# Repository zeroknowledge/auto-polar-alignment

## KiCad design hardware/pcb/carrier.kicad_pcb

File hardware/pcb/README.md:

# APA-CARRIER rev A -- carrier PCB for the Auto Polar Alignment base

Generated by `generate.py` (single reproducible script, see the end of this file). Authoritative design: `SPEC.md`.
**KiCad itself was NOT available: the `.kicad_pcb` / `.kicad_sch` were written by this script and parsed back with kiutils only.
KiCad ERC and DRC have NOT been run and are still outstanding.** Pours are stored as zone outlines; press B (fill all zones) in KiCad.

Board: 85 x 60 mm, 1.6 mm FR4, 2 layers, 2 mm corner radius, four M3 NPTH holes (3.2 mm).
Tallest component: 17.1 mm above the top face (18.7 mm above the bottom face): the plugged-in TMC2209 module with heatsink (assumed envelope). Next tallest: PTC 14 mm, C1 12 mm, C2/C3 11 mm, screw terminals 10 mm (all assumed typical). The J1 socket protrudes 8.5 mm below the board.

## Spec problems found (SPEC.md was not silently changed)

1. **TMC2209 socket row spacing (mechanical, was a real error)**: SPEC.md said 15.24 mm, so a real module would not plug in; the real Pololu/SilentStepStick pin rows are 12.70 mm apart (15.24 x 20.32 mm is the module *size*). The lead has since corrected SPEC.md; the generator default is now 12.70 mm (`--driver-row-spacing`).
2. **Via vs. annular-ring rule**: vias 0.6/0.3 mm have a 0.15 mm ring while "plated through-hole annular ring >= 0.3 mm" is also stated. I applied 0.3 mm to component holes and 0.15 mm to vias (fab capability not checked).
3. **PTC voltage rating**: the TVS (1.5KE18A) clamps near 25 V, so choose PTCs rated for at least 24-30 V; many 16 V radial PTCs do not have a 5.08 mm lead pitch (not verified against a specific part).
4. 3V3 track width not specified (0.5 mm used). With D1 in series the motor rail is about 0.4-0.5 V below the PD voltage (not an error).

## Files

| File | What |
|---|---|
| `netlist.json` | single source of truth (parts, pins, nets, NC pins); `carrier.net` is the same netlist in KiCad format |
| `diagrams/` | schematic sheets and system wiring diagram (SVG/PDF/PNG), drawn from `netlist.json` by `make_diagrams.py` (not part of this script) |
| `carrier.kicad_pro`, `carrier.kicad_pcb`, `carrier.kicad_sch` | KiCad 8 project (written, not opened in KiCad) |
| `fab/carrier-*.gtl/.gbl/.gts/.gbs/.gtp/.gto/.gbo/.gm1`, `fab/carrier-PTH.drl`, `fab/carrier-NPTH.drl`, `fab/carrier_gerbers.zip` | Gerber RS-274X (F.Cu, B.Cu, F/B mask, F paste, F/B silkscreen, Edge.Cuts) and Excellon drills |
| `fab/gerber_reparse_preview.png` | the Gerbers re-read with gerbonara and re-drawn (proof they parse) |
| `carrier_bom.csv`, `carrier_cpl.csv` | BOM (grouped, plug-in items listed but marked not soldered) and SMD pick-and-place |
| `carrier_outline.dxf`, `carrier_board.stl` | outline/holes/component keep-outs/Pi outline; extruded board + component envelopes |
| `carrier_top.png`, `carrier_bottom.png` | renders |
| `verification_report.json` | every number quoted below |

## Pin map

### Pi header J1 (female socket on the BOTTOM side; pin 1 = square pad, lower-left row when viewed from the top)

| Pi pin | GPIO | Net |
|---|---|---|
| 1 |  | 3V3 |
| 2 |  | 5V_PI |
| 3 | GPIO2 SDA1 | SDA |
| 4 |  | 5V_PI |
| 5 | GPIO3 SCL1 | SCL |
| 6 |  | GND |
| 7 |  | NC |
| 8 | GPIO14 TXD | UART_TX_RAW |
| 9 |  | GND |
| 10 | GPIO15 RXD | UART_BUS |
| 11 | GPIO17 | STEP_AZ |
| 12 |  | NC |
| 13 | GPIO27 | DIR_AZ |
| 14 |  | GND |
| 15 | GPIO22 | EN_AZ |
| 16 | GPIO23 | STEP_ALT |
| 17 |  | 3V3 |
| 18 | GPIO24 | DIR_ALT |
| 19 |  | NC |
| 20 |  | GND |
| 21 |  | NC |
| 22 | GPIO25 | EN_ALT |
| 23 |  | NC |
| 24 |  | NC |
| 25 |  | GND |
| 26 |  | NC |
| 27 |  | NC |
| 28 |  | NC |
| 29 | GPIO5 | ES_AZ_MIN |
| 30 |  | GND |
| 31 | GPIO6 | ES_AZ_MAX |
| 32 |  | NC |
| 33 | GPIO13 | ES_ALT_MIN |
| 34 |  | GND |
| 35 | GPIO19 | ES_ALT_MAX |
| 36 |  | NC |
| 37 | GPIO26 | SPARE |
| 38 |  | NC |
| 39 |  | GND |
| 40 |  | NC |

27 pins used, 13 NC (pins 7, 12, 19, 21, 23, 24, 26, 27, 28, 32, 36, 38, 40 carry no copper connection).

### TMC2209 sockets (rows 12.7 mm apart; U1 = azimuth, U2 = altitude)

| U1/U2 row A pin | U1 net | U2 net | row B pin | U1 net | U2 net |
|---|---|---|---|---|---|
| A1 EN | EN_AZ | EN_ALT | B1 VM | +12V | +12V |
| A2 MS1 | GND | 3V3 | B2 GND | GND | GND |
| A3 MS2 | GND | GND | B3 COIL_A2 | AZ_COIL_A2 | ALT_COIL_A2 |
| A4 PDN_UART | UART_BUS | UART_BUS | B4 COIL_A1 | AZ_COIL_A1 | ALT_COIL_A1 |
| A5 PDN_UART_ALT | NC | NC | B5 COIL_B1 | AZ_COIL_B1 | ALT_COIL_B1 |
| A6 CLK | GND | GND | B6 COIL_B2 | AZ_COIL_B2 | ALT_COIL_B2 |
| A7 STEP | STEP_AZ | STEP_ALT | B7 VIO | 3V3 | 3V3 |
| A8 DIR | DIR_AZ | DIR_ALT | B8 GND | GND | GND |

B3..B6 go straight to J5 (AZ) / J6 (ALT) pins 1..4. End stops: J7..J10 pin 1 = signal (net `ES_*_IN`) -> 1 kOhm (R4..R7) -> GPIO net -> 100 nF to GND; pin 2 = GND.
I2C headers J11 (IMU) / J12 (GNSS): 1 GND, 2 3V3, 3 5V_F, 4 SDA, 5 SCL. Power: see `SPEC.md`; netlist cross-checks are in `netlist.json` ("verification").

## Placement decisions and assumptions

- **Pi stack.** Pi Zero 2 W geometry is from the official mechanical drawing RP-008358-DS (read from the PDF's vector data): 65 x 30 mm, mounting holes 3.5 mm from the edges, 40-pin header centred on the 65 mm edge with its two rows on the hole centreline (3.5 mm from the top edge), pin 1 = square pad at the left end of the inner row. J1 is centred on the carrier at x = 42.418 mm, y = 12.446 mm (12.4 mm from the south long edge); the Pi hangs below J1 and its body sticks 14.1 mm out of the south edge, so the USB and mini-HDMI connectors (bottom long edge of the Pi) stay uncovered. The carrier is 20 mm wider than the Pi (10 mm each side); the SD slot (left short edge) and CSI connector (right short edge) are reached from the sides, 11 mm below the carrier underside (check this against your enclosure). The silkscreen shows the Pi top edge, its two short edges (clipped at the board edge) and the two Pi mounting holes; the full 65 x 30 outline is in `carrier_outline.dxf` layer `PI_OUTLINE`. This is my reading of the SPEC sentence "the board overhangs the Pi so USB/HDMI/camera connectors stay uncovered"; the spec text "J1 along one long edge" is met loosely (J1 sits in the southern 20 % of the board, the south zone holds the end-stop connectors and filters that use the odd J1 pins).
- **Why J1 is not on the very edge.** The odd (south) row of J1 carries 10 signals. On a 2-layer board they can only leave through the 0.94 mm gaps between the 1.6 mm pads (0.3 mm track, 0.32 mm clearance) or around the ends of the header. The three AZ step/dir/enable signals use hand-placed waypoints through those gaps (`PREROUTE` in the script); everything else is autorouted.
- **TMC2209 modules.** Rows 12.7 mm apart (the lead corrected SPEC.md from 15.24 mm; Pololu A4988 drawing: board 15.2 x 20.3 mm, rows 12.70 mm apart). The BIGTREETECH TMC2209 is *assumed* to share the Pololu / SilentStepStick footprint: **unverified** for the V1.3 board; its pin order is from the generic BTT wiki page (global.bttwiki.com/TMC2209.html), also **not confirmed for V1.3**. Module bodies U1/U2 are 9.5 mm apart (>= 1 mm required) and no tall part is within 1 mm of a module. Module envelope assumed 15.24 x 20.32 mm, top at 17.1 mm above the socket seat (heatsink included).
- **Footprints** follow the KiCad official library (GitLab `kicad-footprints`, read at build time): JST XH B2B/B4B-XH-A (pads 1.7 x 1.95, drill 0.95, body 5.75 deep), DO-201AD (pad 3.2, drill 1.6, P12.70 variant), Phoenix MKDS-1,5-2-5.08 terminal (pad 2.6, drill 1.3, 10.2 x 9.8), radial electrolytics (pad 1.6, drill 0.8). The 2.54 mm header pads are 1.6 mm (drill 1.0, ring exactly 0.30 mm). **Unverified:** the PTC envelope (10 x 4 x 14 mm assumed), electrolytic and terminal heights (12/11/10 mm typical), JST height 7 mm, socket body heights 8.5 mm. Screw-terminal wire entry is assumed to face the nearest board edge.
- **Track widths.** 0.8 mm for 12 V, motor coil and 5 V nets (about 2 A at 10 K rise, IPC-2221); 0.5 mm for 3V3 (SPEC gives no width for it); 0.3 mm for signals. Vias 0.6 / 0.3 mm. GND is a pour on both layers with 0.3 mm thermal gaps, 0.5 mm spokes and 133 stitching vias on a 5 mm grid.
- **R2, R3, C8, C9** (0805, 0.6 mm tall) sit in the pocket between the two socket rows, under the plugged-in module (8.5 mm of headroom). **J11/J12 labels** share one label column between the two headers. These silk texts could not be placed without overlapping pads or other silk and were omitted (J7..J10 per-pin SIG/GND labels are among them; some J1/module pin labels too): +12V, 5V_PI, ALT MOTOR, AZ MOTOR, EN, ES1-4 = AZ MIN, AZ MAX, ALT MIN, ALT MAX, GND, MS1, RXD, SAL, SIG, VIO. Pin 1 of every header is a square pad; the connectors' pin 2 is GND.

## Verification (all numbers from this run, see `verification_report.json`)

- **Netlist** (22/22 checks): every net has >= 2 pins; no pin on two nets; only the SPEC NC pins unconnected; all 40 J1 pins and all 32 socket pins re-derived from the tables parsed out of `SPEC.md`.
- **Routing**: 145 track polylines, 607.5 mm, 8 signal/power vias; 35/35 routable nets routed (GND is the pour).
- **Copper connectivity**: 36/36 nets form exactly one connected copper component (tracks, vias, THT pads and pours counted); shorts found: 0. GND: 38 pads in 1 component.
- **Clearance**: minimum clearance between different nets **0.291 mm** (rule 0.25 mm), violations: 0; by type: {'pad/pour': 0.299, 'pad/track': 0.307, 'pad/via': 0.291, 'pour/track': 0.299, 'pour/via': 0.3, 'track/track': 0.335, 'track/via': 0.312}. Minimum copper-to-board-edge 0.500 mm (rule 0.5 mm). Minimum PTH annular ring 0.300 mm (J1.1); minimum hole-to-hole 0.900 mm; minimum hole-to-edge 1.85 mm; NPTH-to-copper 0.50 mm. Minimum track width 0.3 mm.
- **Checker self-test** (to show the checks can fail): {'delete_one_SPARE_track_gives_open': True, 'rogue_track_gives_short': True, 'rogue_track_gives_clearance_violation': True, 'near_miss_track_gives_clearance_violation': True}.
- **Gerbers** (re-read with gerbonara 0.13.0):

| file | extent | result |  |
|---|---|---|---|
| carrier-F_Cu.gtl | bbox [0.5, 0.5, 84.5, 59.5] | replayed-vs-generated difference 0.000298 mm2 | OK |
| carrier-B_Cu.gbl | bbox [0.5, 0.5, 84.5, 59.5] | replayed-vs-generated difference 0.000221 mm2 | OK |
| carrier-F_Mask.gts | bbox [1.85, 1.85, 83.15, 58.15] | replayed-vs-generated difference 0.000127 mm2 | OK |
| carrier-B_Mask.gbs | bbox [1.85, 1.85, 83.15, 58.15] | replayed-vs-generated difference 0.000126 mm2 | OK |
| carrier-F_Paste.gtp | bbox [3.3, 7.3, 73.725, 33.025] | replayed-vs-generated difference 0.0 mm2 | OK |
| carrier-F_Silkscreen.gto | bbox [1.71, 0.35, 80.938, 59.59] | replayed-vs-generated difference 0.000472 mm2 | OK |
| carrier-B_Silkscreen.gbo | bbox [16.928, 9.816, 67.908, 15.076] | replayed-vs-generated difference 0.0 mm2 | OK |
| carrier-Edge_Cuts.gm1 | bbox [-0.05, -0.05, 85.05, 60.05] | outline + 0.05 mm aperture half-width: True |  |
| carrier-PTH.drl | 266 holes | positions/diameters identical to generator: True |  |
| carrier-NPTH.drl | 4 holes | positions/diameters identical to generator: True |  |

- **KiCad PCB** parsed back with kiutils: 46 footprints, 155 pads compared with `netlist.json`: **0 mismatches**; 199 segments, 141 vias, 2 zones, 36 nets; independent copper connectivity rebuilt from the file (non-GND nets): 0 opens.
- **KiCad schematic** parsed back with kiutils: 46 symbols, 140 wire stubs with net labels, 15 no-connect flags; pin->net resolved from the parsed wires/labels/library pins for 155 pins: **0 mismatches** against `netlist.json` (net-label style, no ERC run).
- **DXF/STL**: DXF outline bbox [0.0, -0.0, 85.0, 60.0] (area difference to the outline 0.015 mm2), 129/129 hole circles; STL bbox [0.0, 0.0, -8.5] .. [85.0, 60.0, 18.7] mm (71792 triangles), board-only volume 7922.0 mm3 vs area x thickness 7922.0 mm3.

## NOT verified / outstanding

- **KiCad ERC and DRC have not been run** (KiCad is not installed); the KiCad files have never been opened in KiCad. Zones are unfilled in the file until KiCad refills them; KiCad's own fill may differ in detail from the pour in the Gerbers.
- No fab DFM / online Gerber viewer check; Gerbers were only re-read with gerbonara. Solder-mask, paste and silkscreen rules are the generator's own (0.05 mm mask expansion, vias tented, silk >= 1 mm high, 0.18 mm stroke).
- Component heights and the PTC/electrolytic/terminal envelopes, JLCPCB-style CPL rotations and the TMC2209 V1.3 footprint/pin order are unverified (see above).
- No electrical simulation; current ratings are hand estimates.

## Sources used

- Raspberry Pi Zero 2 W mechanical drawing, RP-008358-DS (pip.raspberrypi.com), and Raspberry Pi documentation (raspberrypi.com/documentation/computers/zero.html, 65 mm x 30 mm).
- KiCad official footprint library `kicad-footprints` (gitlab.com/kicad/libraries): `Connector_JST`, `Diode_THT`, `TerminalBlock_Phoenix`, `Capacitor_THT`, `Connector_PinSocket_2.54mm`, `Module/Pololu_Breakout-16_15.2x20.3mm` (pad rows 12.7 mm apart).
- Pololu A4988 / DRV8825 dimension drawing and Pololu forum reply (0.5 in row spacing); BIGTREETECH TMC2209 wiki (global.bttwiki.com/TMC2209.html).

## Regenerating

```
python3 -m venv env && env/bin/pip install kiutils gerbonara ezdxf shapely numpy scipy matplotlib trimesh manifold3d mapbox-earcut pillow
env/bin/python generate.py                       # default driver row spacing 12.70 mm
env/bin/python generate.py --driver-row-spacing 15.24 --out /some/dir   # spec's old value: still routes, but reports a J6/D2 courtyard overlap, so the north-side placement would need re-spacing
```
Run time is about 30 s on a laptop (routing is a pure-Python A*; two consecutive runs give byte-identical Gerbers, KiCad files and netlist). The only non-deterministic input is the run date printed on the silkscreen.

## Cautions (added by the lead after the software review)

- J11/J12 pin 3 carries 5V_F. Power I2C breakouts from 3V3 (pin 2) unless they are known to level-shift: a 5 V pull-up on SDA/SCL can destroy the Pi's GPIO.
- Check the TMC2209 module's pin 4 (PDN_UART versus DIAG/INDEX) against its drawing before plugging both modules in.
- End stops are wired common + normally-closed (see SPEC.md): a pressed or broken switch reads HIGH.

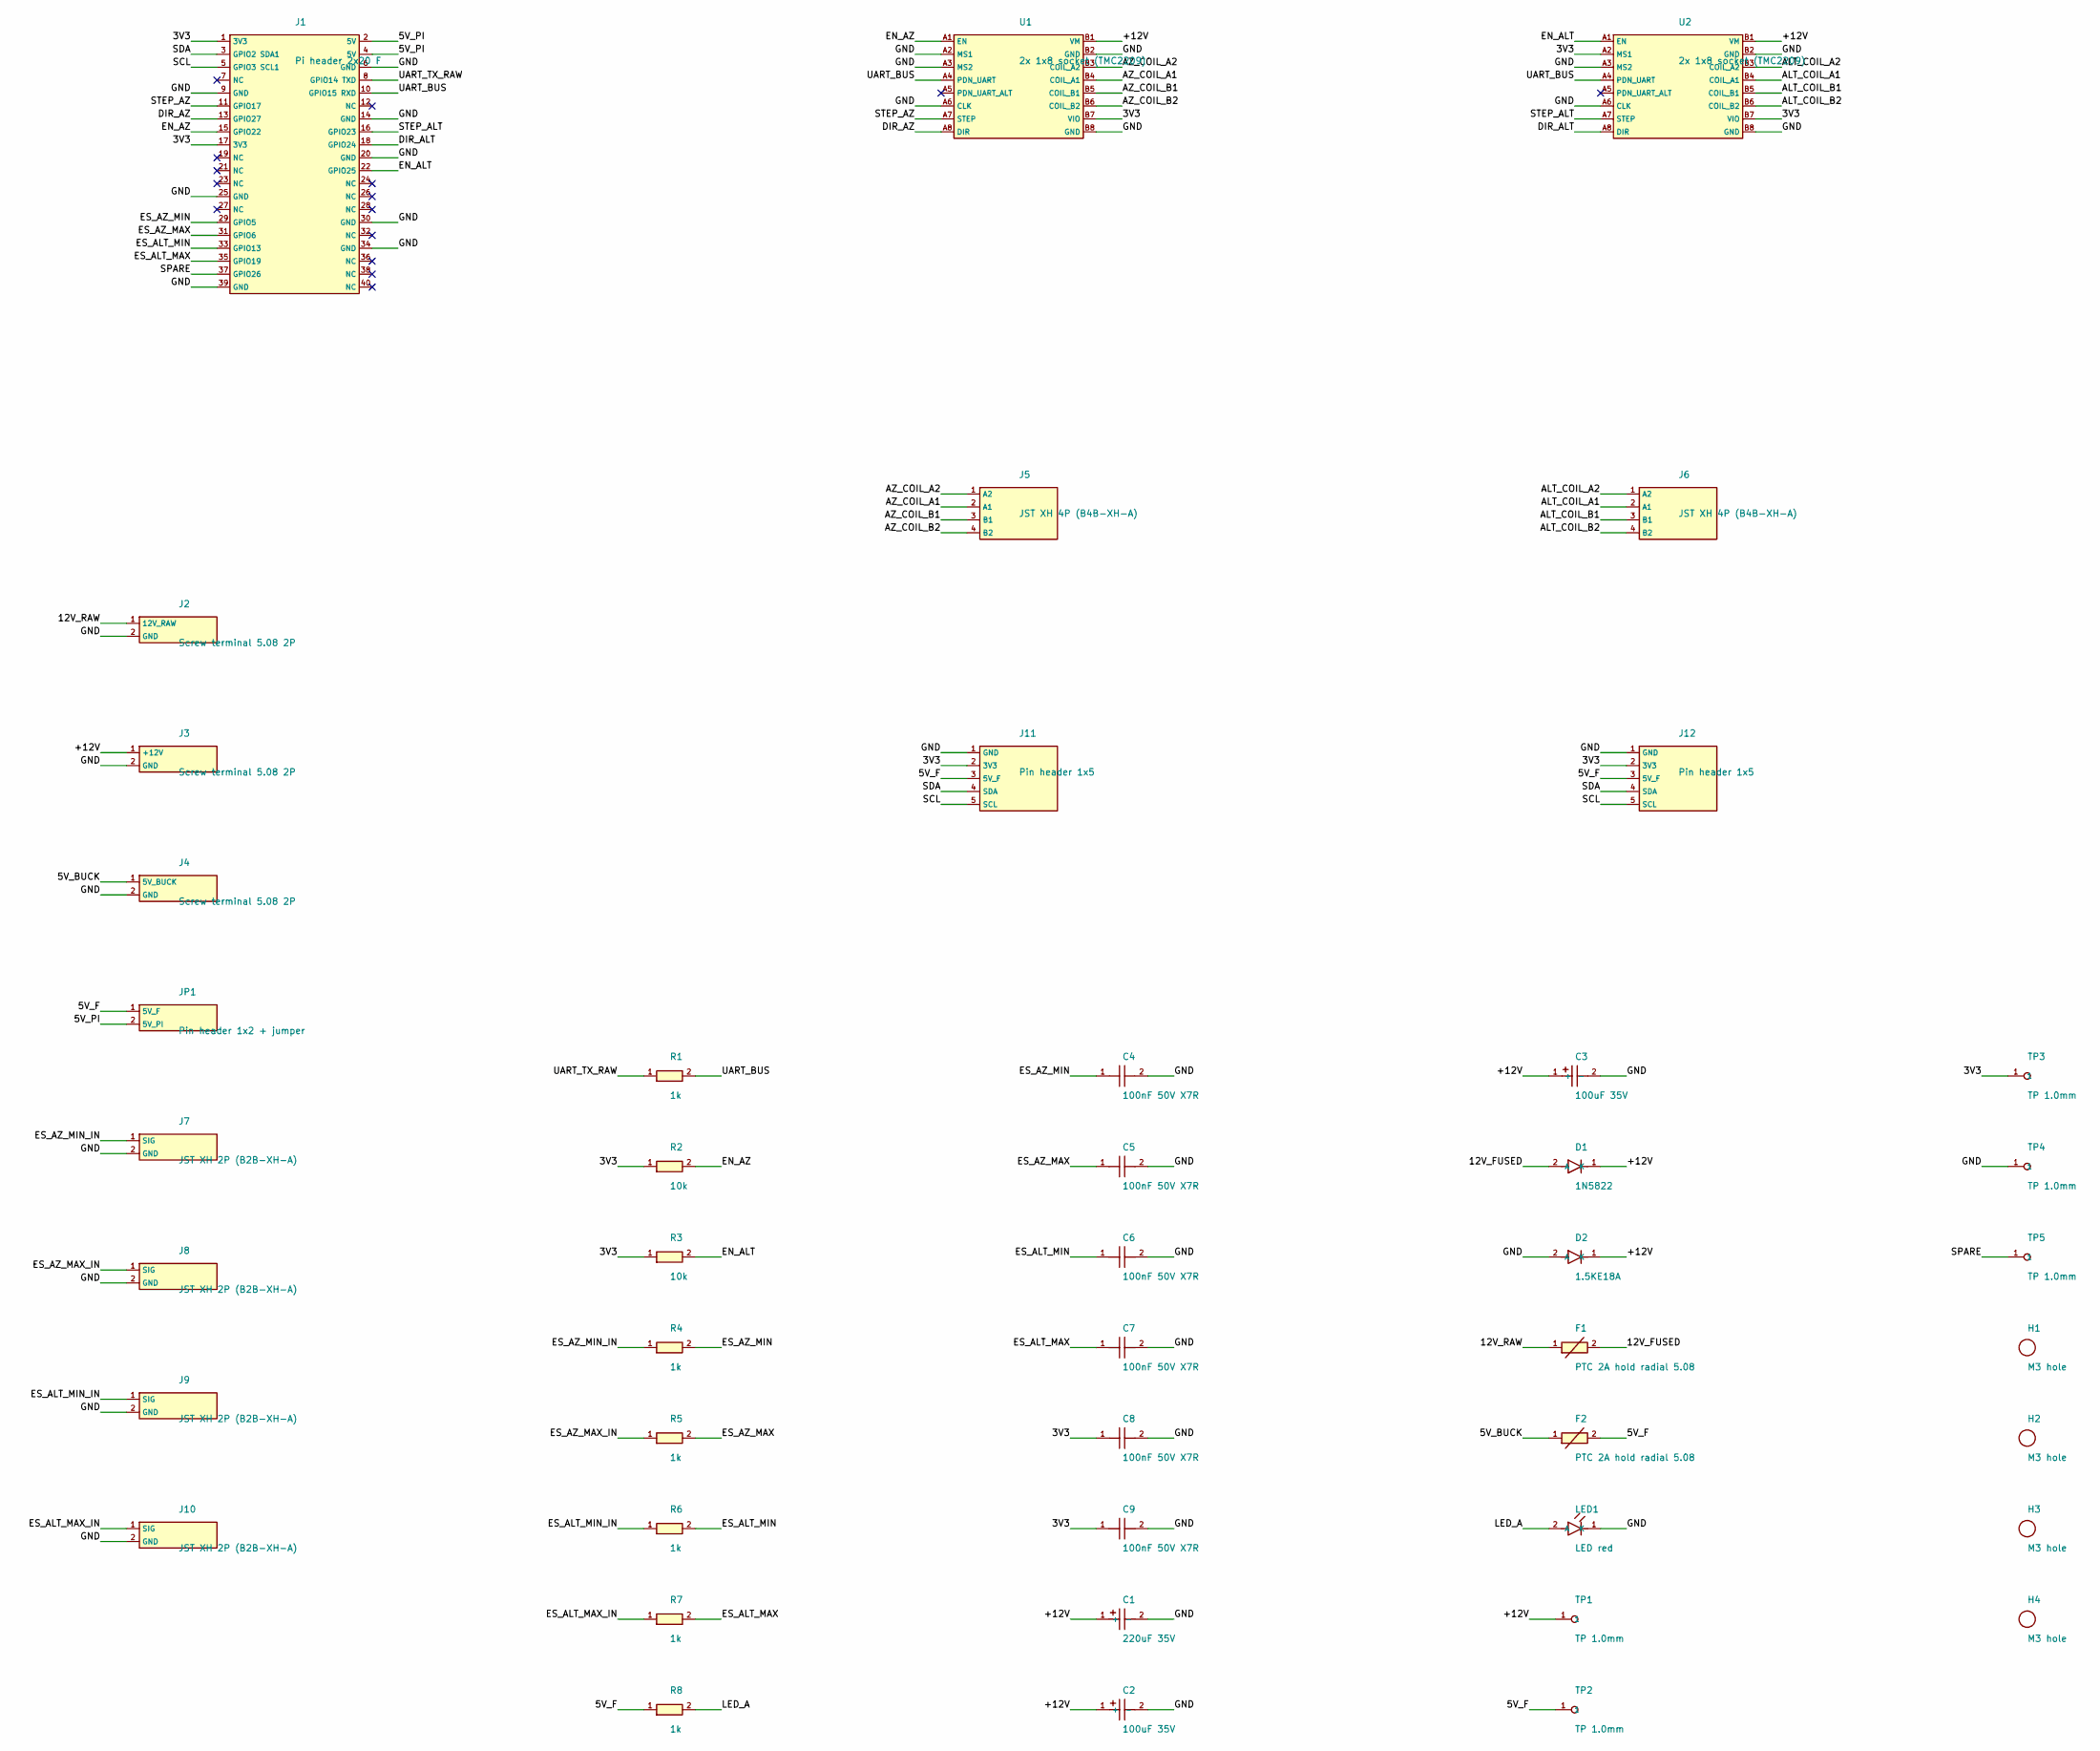
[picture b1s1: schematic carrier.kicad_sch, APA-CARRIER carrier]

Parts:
C1: 220uF 35V; CP_Radial_D8.0mm_P3.50mm
C2, C3: 100uF 35V; CP_Radial_D6.3mm_P2.50mm
C4, C5, C6, C7, C8, C9: 100nF 50V X7R; R_0805_2012Metric
D1: 1N5822; D_DO-201AD_P12.70mm_Horizontal
D2: 1.5KE18A; D_DO-201AD_P12.70mm_Horizontal
F1, F2: PTC 2A hold radial 5.08; PTC_Radial_P5.08mm
H1, H2, H3, H4: M3 hole; MountingHole_3.2mm_M3_NPTH
J1: Pi header 2x20 F; PinSocket_2x20_P2.54mm_Vertical_BOTTOM
J2, J3, J4: Screw terminal 5.08 2P; TerminalBlock_5.08mm_1x02_Horizontal
J5, J6: JST XH 4P (B4B-XH-A); JST_XH_B4B-XH-A_1x04_P2.50mm_Vertical
J7, J8, J9, J10: JST XH 2P (B2B-XH-A); JST_XH_B2B-XH-A_1x02_P2.50mm_Vertical
J11, J12: Pin header 1x5; PinHeader_1x05_P2.54mm_Vertical
JP1: Pin header 1x2 + jumper; PinHeader_1x02_P2.54mm_Vertical
LED1: LED red; LED_0805_2012Metric
R1, R4, R5, R6, R7, R8: 1k; R_0805_2012Metric
R2, R3: 10k; R_0805_2012Metric
TP1, TP2, TP3, TP4, TP5: TP 1.0mm; TestPoint_THT_D1.8mm_Drill1.0mm
U1, U2: 2x 1x8 socket (TMC2209); PinSocket_2x08_Rows_P2.54mm

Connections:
3V3: C8.1, C9.1, J1.1 (3V3), J1.17 (3V3), J11.2 (3V3), J12.2 (3V3), R2.1, R3.1, TP3.1, U1.B7 (VIO), U2.A2 (MS1), U2.B7 (VIO)
5V_BUCK: F2.1, J4.1 (5V_BUCK)
5V_F: F2.2, J11.3 (5V_F), J12.3 (5V_F), JP1.1 (5V_F), R8.1, TP2.1
5V_PI: J1.2 (5V), J1.4 (5V), JP1.2 (5V_PI)
12V_FUSED: D1.2 (A), F1.2
12V_RAW: F1.1, J2.1 (12V_RAW)
+12V: C1.1 (+), C2.1 (+), C3.1 (+), D1.1 (K), D2.1 (K), J3.1 (+12V), TP1.1, U1.B1 (VM), U2.B1 (VM)
ALT_COIL_A1: J6.2 (A1), U2.B4 (COIL_A1)
ALT_COIL_A2: J6.1 (A2), U2.B3 (COIL_A2)
ALT_COIL_B1: J6.3 (B1), U2.B5 (COIL_B1)
ALT_COIL_B2: J6.4 (B2), U2.B6 (COIL_B2)
AZ_COIL_A1: J5.2 (A1), U1.B4 (COIL_A1)
AZ_COIL_A2: J5.1 (A2), U1.B3 (COIL_A2)
AZ_COIL_B1: J5.3 (B1), U1.B5 (COIL_B1)
AZ_COIL_B2: J5.4 (B2), U1.B6 (COIL_B2)
DIR_ALT: J1.18 (GPIO24), U2.A8 (DIR)
DIR_AZ: J1.13 (GPIO27), U1.A8 (DIR)
EN_ALT: J1.22 (GPIO25), R3.2, U2.A1 (EN)
EN_AZ: J1.15 (GPIO22), R2.2, U1.A1 (EN)
ES_ALT_MAX: C7.1, J1.35 (GPIO19), R7.2
ES_ALT_MAX_IN: J10.1 (SIG), R7.1
ES_ALT_MIN: C6.1, J1.33 (GPIO13), R6.2
ES_ALT_MIN_IN: J9.1 (SIG), R6.1
ES_AZ_MAX: C5.1, J1.31 (GPIO6), R5.2
ES_AZ_MAX_IN: J8.1 (SIG), R5.1
ES_AZ_MIN: C4.1, J1.29 (GPIO5), R4.2
ES_AZ_MIN_IN: J7.1 (SIG), R4.1
GND: C1.2 (-), C2.2 (-), C3.2 (-), C4.2, C5.2, C6.2, C7.2, C8.2, C9.2, D2.2 (A), J1.6 (GND), J1.9 (GND), J1.14 (GND), J1.20 (GND), J1.25 (GND), J1.30 (GND), J1.34 (GND), J1.39 (GND), J2.2 (GND), J3.2 (GND), J4.2 (GND), J7.2 (GND), J8.2 (GND), J9.2 (GND), J10.2 (GND), J11.1 (GND), J12.1 (GND), LED1.1 (K), TP4.1, U1.A2 (MS1), U1.A3 (MS2), U1.A6 (CLK), U1.B2 (GND), U1.B8 (GND), U2.A3 (MS2), U2.A6 (CLK), U2.B2 (GND), U2.B8 (GND)
LED_A: LED1.2 (A), R8.2
SCL: J1.5 (GPIO3 SCL1), J11.5 (SCL), J12.5 (SCL)
SDA: J1.3 (GPIO2 SDA1), J11.4 (SDA), J12.4 (SDA)
SPARE: J1.37 (GPIO26), TP5.1
STEP_ALT: J1.16 (GPIO23), U2.A7 (STEP)
STEP_AZ: J1.11 (GPIO17), U1.A7 (STEP)
UART_BUS: J1.10 (GPIO15 RXD), R1.2, U1.A4 (PDN_UART), U2.A4 (PDN_UART)
UART_TX_RAW: J1.8 (GPIO14 TXD), R1.1

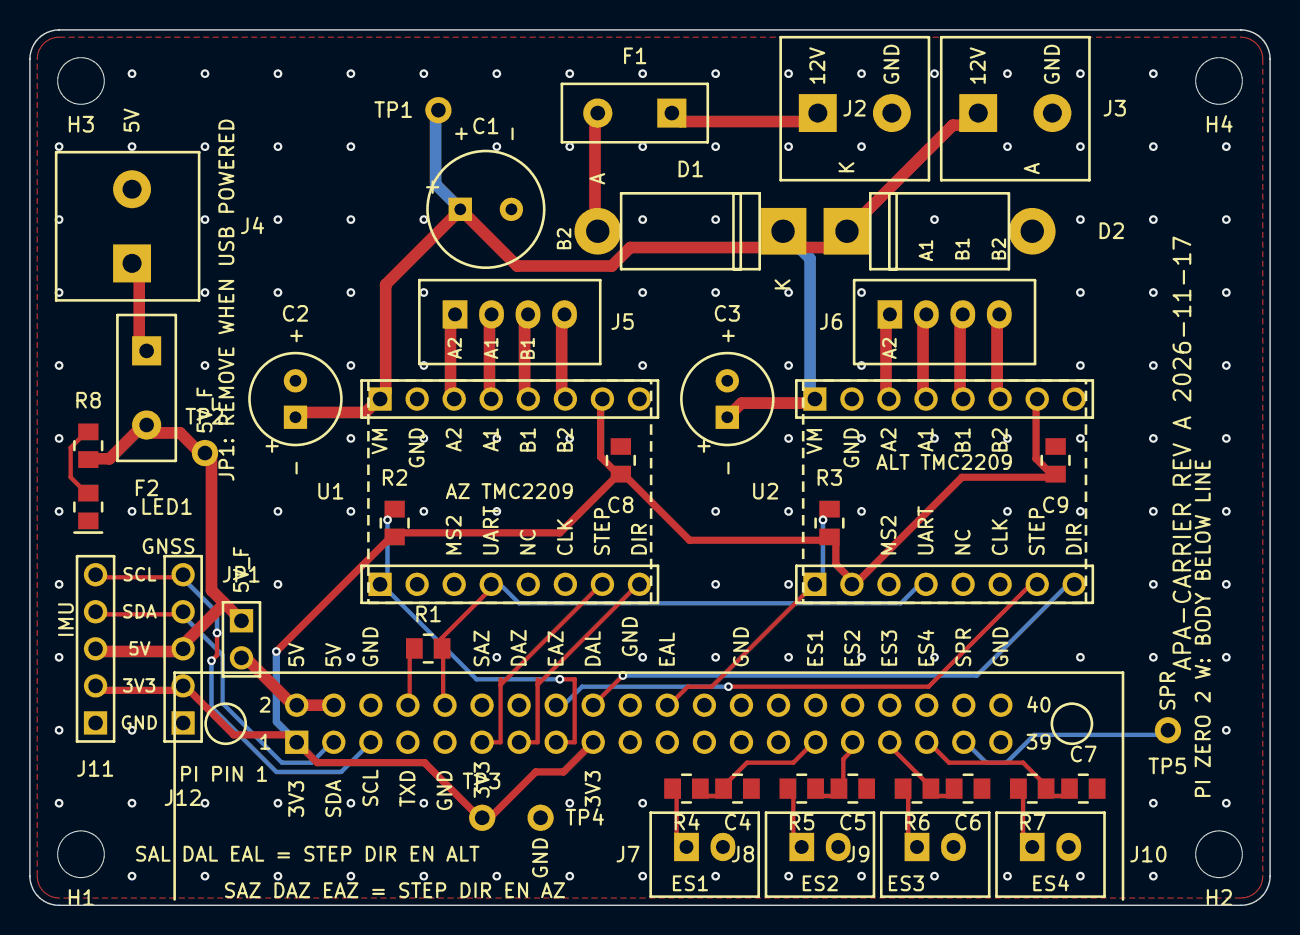
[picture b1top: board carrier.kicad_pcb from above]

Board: 2 copper layers, 85.0 x 60.0 mm, 46 parts (1 on the bottom side), 36 nets.

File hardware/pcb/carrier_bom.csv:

Comment,Designator,Footprint,Quantity,Description,MPN / note,Mounting
Pi header 2x20 F,J1,PinSocket_2x20_P2.54mm_Vertical_BOTTOM,1,"Raspberry Pi 40-pin socket, 2.54 mm, mounted on BOTTOM side",,"THT (bottom side, socket)"
2x 1x8 socket (TMC2209),"U1,U2",PinSocket_2x08_Rows_P2.54mm,2,Two 1x8 female 2.54 mm sockets for a TMC2209 module,,THT
Screw terminal 5.08 2P,"J2,J3,J4",TerminalBlock_5.08mm_1x02_Horizontal,3,"Screw terminal, 5.08 mm pitch, 2 pin",,THT
JST XH 4P (B4B-XH-A),"J5,J6",JST_XH_B4B-XH-A_1x04_P2.50mm_Vertical,2,"JST XH 2.5 mm, 4 pin, vertical",B4B-XH-A,THT
JST XH 2P (B2B-XH-A),"J7,J8,J9,J10",JST_XH_B2B-XH-A_1x02_P2.50mm_Vertical,4,"JST XH 2.5 mm, 2 pin, vertical",B2B-XH-A,THT
Pin header 1x5,"J11,J12",PinHeader_1x05_P2.54mm_Vertical,2,1x5 2.54 mm header,,THT
Pin header 1x2 + jumper,JP1,PinHeader_1x02_P2.54mm_Vertical,1,1x2 jumper header,,THT
PTC 2A hold radial 5.08,"F1,F2",PTC_Radial_P5.08mm,2,"Radial resettable fuse, 2 A hold",,THT
1N5822,D1,D_DO-201AD_P12.70mm_Horizontal,1,Schottky 3 A 40 V axial,1N5822,THT
1.5KE18A,D2,D_DO-201AD_P12.70mm_Horizontal,1,TVS 1500 W 18 V unidirectional axial,1.5KE18A,THT
220uF 35V,C1,CP_Radial_D8.0mm_P3.50mm,1,Electrolytic 220 uF 35 V radial,,THT
100uF 35V,"C2,C3",CP_Radial_D6.3mm_P2.50mm,2,Electrolytic 100 uF 35 V radial,,THT
100nF 50V X7R,"C4,C5,C6,C7,C8,C9",R_0805_2012Metric,6,Ceramic 100 nF 50 V X7R,,SMD (top)
1k,"R1,R4,R5,R6,R7,R8",R_0805_2012Metric,6,Resistor 1 kOhm,,SMD (top)
10k,"R2,R3",R_0805_2012Metric,2,Resistor 10 kOhm,,SMD (top)
LED red,LED1,LED_0805_2012Metric,1,"Red LED 0805 (pin1 = cathode, pin2 = anode)",,SMD (top)
TP 1.0mm,"TP1,TP2,TP3,TP4,TP5",TestPoint_THT_D1.8mm_Drill1.0mm,5,"Test point, 1.0 mm drill",,THT
M3 mounting hole (NPTH 3.2 mm),"H1,H2,H3,H4",MountingHole_3.2mm_M3_NPTH,4,"board feature only, no part",,none
"TMC2209 module, 0.6x0.8 in, SilentStepStick/Pololu pinout (e.g. BIGTREETECH V1.3)","(U1,U2 plug-in)",plugs into U1/U2 sockets,2,NOT soldered; buy separately,,plug-in
2.54 mm jumper shunt,(JP1 plug-in),fits JP1,1,NOT soldered; buy separately,,plug-in

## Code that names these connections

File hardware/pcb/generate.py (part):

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    18: "DIR_ALT", 20: "GND", 22: "EN_ALT", 25: "GND", 29: "ES_AZ_MIN", 30: "GND", 31: "ES_AZ_MAX",
    33: "ES_ALT_MIN", 34: "GND", 35: "ES_ALT_MAX", 37: "SPARE", 39: "GND",
}
PI_GPIO = {3: "GPIO2 SDA1", 5: "GPIO3 SCL1", 8: "GPIO14 TXD", 10: "GPIO15 RXD", 11: "GPIO17", 13: "GPIO27",
           15: "GPIO22", 16: "GPIO23", 18: "GPIO24", 22: "GPIO25", 29: "GPIO5", 31: "GPIO6", 33: "GPIO13",
           35: "GPIO19", 37: "GPIO26"}

# TMC2209 module pin functions (BIGTREETECH wiki order; V1.3 not confirmed)
MOD_A = ["EN", "MS1", "MS2", "PDN_UART", "PDN_UART_ALT", "CLK", "STEP", "DIR"]
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    "A7": "STEP_ALT", "A8": "DIR_ALT",
    "B1": "+12V", "B2": "GND", "B3": "ALT_COIL_A2", "B4": "ALT_COIL_A1", "B5": "ALT_COIL_B1",
    "B6": "ALT_COIL_B2", "B7": "3V3", "B8": "GND"})
PIN_NET["R1"].update({"1": "UART_TX_RAW", "2": "UART_BUS"})
PIN_NET["R2"].update({"1": "3V3", "2": "EN_AZ"})
PIN_NET["R3"].update({"1": "3V3", "2": "EN_ALT"})

PIN_NET["J2"].update({"1": "12V_RAW", "2": "GND"})
PIN_NET["F1"].update({"1": "12V_RAW", "2": "12V_FUSED"})
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PIN_NET["J4"].update({"1": "5V_BUCK", "2": "GND"})
PIN_NET["F2"].update({"1": "5V_BUCK", "2": "5V_F"})
PIN_NET["JP1"].update({"1": "5V_F", "2": "5V_PI"})
PIN_NET["R8"].update({"1": "5V_F", "2": "LED_A"})
PIN_NET["LED1"].update({"1": "GND", "2": "LED_A"})           # pin1 = cathode, pin2 = anode
PIN_NET["J5"].update({"1": "AZ_COIL_A2", "2": "AZ_COIL_A1", "3": "AZ_COIL_B1", "4": "AZ_COIL_B2"})
PIN_NET["J6"].update({"1": "ALT_COIL_A2", "2": "ALT_COIL_A1", "3": "ALT_COIL_B1", "4": "ALT_COIL_B2"})
ES = [("J7", "R4", "C4", "ES_AZ_MIN"), ("J8", "R5", "C5", "ES_AZ_MAX"),
      ("J9", "R6", "C6", "ES_ALT_MIN"), ("J10", "R7", "C7", "ES_ALT_MAX")]
for j, r, c, n in ES:
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PIN_NET["TP2"].update({"1": "5V_F"})
PIN_NET["TP3"].update({"1": "3V3"})
PIN_NET["TP4"].update({"1": "GND"})
PIN_NET["TP5"].update({"1": "SPARE"})

NETS = OrderedDict()
NC_PINS = []
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        "end-stop RC: R(1k) signal->GPIO net, C(100n) GPIO->GND")
    chk(all(PIN_NET[j] == {"1": "GND", "2": "3V3", "3": "5V_F", "4": "SDA", "5": "SCL"} for j in ("J11", "J12")),
        "J11/J12 1 GND 2 3V3 3 5V_F 4 SDA 5 SCL")
    chk(PIN_NET["R1"] == {"1": "UART_TX_RAW", "2": "UART_BUS"} and PARTS["R1"]["value"] == "1k", "R1 1k TX_RAW->UART_BUS")
    chk(PIN_NET["R2"] == {"1": "3V3", "2": "EN_AZ"} and PIN_NET["R3"] == {"1": "3V3", "2": "EN_ALT"}
        and PARTS["R2"]["value"] == "10k" and PARTS["R3"]["value"] == "10k", "R2/R3 10k pull-ups to 3V3")
    chk([PIN_NET[f"TP{i}"]["1"] for i in range(1, 6)] == ["+12V", "5V_F", "3V3", "GND", "SPARE"], "TP1..TP5 nets")
    chk(PIN_NET["C8"] == {"1": "3V3", "2": "GND"} and PIN_NET["C9"] == {"1": "3V3", "2": "GND"}, "C8/C9 3V3/GND")
    for text, ok in A:
        res.append(("SPEC prose: " + text, ok, ""))
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J1_PIN_X = {k: J1_X + (k - 9.5) * 2.54 for k in range(20)}
J1_ROW_S = J1_Y - 1.27
PREROUTE = {
    "STEP_AZ": [(0, [(J1_PIN_X[5], J1_ROW_S), (J1_PIN_X[5] + 1.27, J1_ROW_S), (J1_PIN_X[5] + 1.27, _gx(122))])],
    "DIR_AZ": [(0, [(J1_PIN_X[6], J1_ROW_S), (J1_PIN_X[6] + 1.27, J1_ROW_S), (J1_PIN_X[6] + 1.27, _gx(122))])],
    "EN_AZ": [(0, [(J1_PIN_X[7], J1_ROW_S), (J1_PIN_X[7] + 1.27, J1_ROW_S), (J1_PIN_X[7] + 1.27, _gx(122))])],
}

# ============================================================================
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
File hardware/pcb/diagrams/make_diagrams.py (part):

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Outputs (SVG, PDF, PNG each) in this folder:
  carrier_schematic_1_power        12 V input, protection, 5 V path, LED, test points
  carrier_schematic_2_pi_drivers   Pi header, TMC2209 sockets, motor connectors, UART/enable networks
  carrier_schematic_3_io           end-stop inputs, I2C sensor headers, spare GPIO
  system_wiring                    whole-system block wiring (power bank to telescope base)

Every label comes from netlist.json. Before drawing, the netlist is checked against the pin assignments in ../SPEC.md
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

GPIO_NAMES = {int(k): v for k, v in NL["pi_gpio_map"].items()}
PI_NAMES = {1: "3V3", 2: "5V", 3: "GPIO2 SDA1", 4: "5V", 5: "GPIO3 SCL1", 6: "GND", 7: "GPIO4", 8: "GPIO14 TXD",
            9: "GND", 10: "GPIO15 RXD", 11: "GPIO17", 12: "GPIO18", 13: "GPIO27", 14: "GND", 15: "GPIO22",
            16: "GPIO23", 17: "3V3", 18: "GPIO24", 19: "GPIO10", 20: "GND", 21: "GPIO9", 22: "GPIO25",
            23: "GPIO11", 24: "GPIO8", 25: "GND", 26: "GPIO7", 27: "ID_SD", 28: "ID_SC", 29: "GPIO5", 30: "GND",
            31: "GPIO6", 32: "GPIO12", 33: "GPIO13", 34: "GND", 35: "GPIO19", 36: "GPIO16", 37: "GPIO26",
            38: "GPIO20", 39: "GND", 40: "GPIO21"}


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    wire(d, ox + 3.4, oy - 0.6, ox + 4.4, oy - 0.6)
    node(d, ox + 4.4, oy - 0.6, "UART_BUS", open_=True)
    T(d, ox + 9.0, oy - 0.6,
      "UART_BUS = Pi RXD (pin 10) directly, plus both PDN_UART pins (single-wire UART:\nTX through 1 k, RX straight on the bus).", fs=8)
    for k, (ref, net) in enumerate((("R2", "EN_AZ"), ("R3", "EN_ALT"))):
        yy = oy - 2.4 - k * 1.8
        node(d, ox, yy, "3V3", ha="left", open_=True)
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def sheet_io():
    d = Drawing()
    d.config(unit=2.4, fontsize=9)
    T(d, 0, 1.6, "APA-CARRIER rev A  -  sheet 3/3: end stops, I2C sensor headers, spare GPIO", fs=13)
    chans = [("J7", "R4", "C4", "ES_AZ_MIN", "J1 pin 29 (GPIO5)"), ("J8", "R5", "C5", "ES_AZ_MAX", "J1 pin 31 (GPIO6)"),
             ("J9", "R6", "C6", "ES_ALT_MIN", "J1 pin 33 (GPIO13)"), ("J10", "R7", "C7", "ES_ALT_MAX", "J1 pin 35 (GPIO19)")]
    for k, (j, r, c, sig, gp) in enumerate(chans):
        y = -1.0 - k * 4.6
        node(d, 0, y, f"{j}.1  {sig}_IN", ha="left", open_=True)
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            stub(d, getattr(blk, f"L_{i}"), "left", pins[str(i)], 1.8)
    T(d, 18.0, -5.4,
      "SDA and SCL go to J1 pins 3 and 5. The Pi Zero already has 1.8 k pull-ups\non those pins, so the carrier adds none. Header pin order: GND, 3V3, 5V_F, SDA, SCL.", fs=8)
    node(d, 18.0, -8.4, "TP5  SPARE  =  J1 pin 37 (GPIO26)", open_=True)
    T(d, 18.0, -10.2, "Test points: TP1 +12V, TP2 5V_F, TP3 3V3, TP4 GND, TP5 SPARE.\nMounting: four M3 holes H1-H4.", fs=8)
    return d

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
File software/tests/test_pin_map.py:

"""The software's pin defaults must equal the carrier PCB netlist (read-only cross-check).

The netlist maps Pi header *pin numbers* to nets; BCM GPIO numbers come from the netlist's own
``pi_gpio_map`` and are re-derived here from the standard Raspberry Pi 40-pin header table so that an
error in either is caught.
"""
import json
from pathlib import Path

import pytest

from polaralign.config import Config

NETLIST = Path(__file__).resolve().parents[2] / "hardware" / "pcb" / "netlist.json"

# physical header pin -> BCM GPIO (standard Raspberry Pi 40-pin header; GPIO-only pins)
PI_HEADER_BCM = {3: 2, 5: 3, 7: 4, 8: 14, 10: 15, 11: 17, 12: 18, 13: 27, 15: 22, 16: 23, 18: 24, 19: 10, 21: 9,
                 22: 25, 23: 11, 24: 8, 26: 7, 27: 0, 28: 1, 29: 5, 31: 6, 32: 12, 33: 13, 35: 19, 36: 16, 37: 26,
                 38: 20, 40: 21}

pytestmark = pytest.mark.skipif(not NETLIST.exists(), reason="hardware/pcb/netlist.json not present")


@pytest.fixture(scope="module")
def net():
    data = json.loads(NETLIST.read_text())
    parts = {p["ref"]: p for p in data["parts"]}
    j1 = parts["J1"]["pins"]                             # header pin -> net
    by_net = {n: int(pin) for pin, n in j1.items() if n}
    return data, parts, by_net


def test_netlist_gpio_numbers_match_standard_header(net):
    data, parts, _ = net
    for pin, label in data["pi_gpio_map"].items():
        bcm = int(label.split()[0].removeprefix("GPIO"))
        assert PI_HEADER_BCM[int(pin)] == bcm, f"header pin {pin}: netlist says {label}, standard table says GPIO{PI_HEADER_BCM[int(pin)]}"


def test_config_defaults_match_netlist(net):
    _, _, by_net = net
    bcm = {n: PI_HEADER_BCM[pin] for n, pin in by_net.items() if pin in PI_HEADER_BCM}
    m = Config().motion
    assert (m.az.step_pin, m.az.dir_pin, m.az.enable_pin) == (bcm["STEP_AZ"], bcm["DIR_AZ"], bcm["EN_AZ"])
    assert (m.alt.step_pin, m.alt.dir_pin, m.alt.enable_pin) == (bcm["STEP_ALT"], bcm["DIR_ALT"], bcm["EN_ALT"])
    assert (m.az.endstop_min_pin, m.az.endstop_max_pin) == (bcm["ES_AZ_MIN"], bcm["ES_AZ_MAX"])
    assert (m.alt.endstop_min_pin, m.alt.endstop_max_pin) == (bcm["ES_ALT_MIN"], bcm["ES_ALT_MAX"])
    assert bcm["SPARE"] == 26


def test_i2c_and_uart_pins(net):
    _, _, by_net = net
    assert PI_HEADER_BCM[by_net["SDA"]] == 2 and PI_HEADER_BCM[by_net["SCL"]] == 3          # I2C bus 1
    assert PI_HEADER_BCM[by_net["UART_TX_RAW"]] == 14 and PI_HEADER_BCM[by_net["UART_BUS"]] == 15   # /dev/ttyAMA0


def test_uart_addresses_follow_ms1_ms2_strapping(net):
    """TMC2209 slave address = MS1 + 2*MS2; U1 = azimuth, U2 = altitude."""
    _, parts, _ = net
    def address(ref):
        pins = parts[ref]["pins"]
        level = lambda n: 1 if n == "3V3" else 0
        return level(pins["A2"]) + 2 * level(pins["A3"])
    cfg = Config().motion
    assert address("U1") == cfg.az.uart_address == 0
    assert address("U2") == cfg.alt.uart_address == 1


def test_single_wire_uart_topology(net):
    """GPIO14 -> R1 -> bus; GPIO15 on the bus; both drivers' PDN_UART on the bus (echo must be discarded)."""
    data, _, _ = net
    bus = {tuple(p) for p in data["nets"]["UART_BUS"]}
    assert ("U1", "A4") in bus and ("U2", "A4") in bus and ("J1", "10") in bus
    assert ("R1", "2") in bus
    assert ("R1", "1") in {tuple(p) for p in data["nets"]["UART_TX_RAW"]}


def test_enable_pins_have_pullups_so_drivers_are_off_at_boot(net):
    data, parts, _ = net
    for en, res in (("EN_AZ", "R2"), ("EN_ALT", "R3")):
        assert res in {p[0] for p in data["nets"][en]}, f"{en} has no pull-up resistor"
        assert parts[res]["value"].startswith("10")
    assert Config().motion.az.enable_pin and True


def test_endstop_inputs_have_series_resistor_and_filter_cap(net):
    data, _, _ = net
    for es in ("ES_AZ_MIN", "ES_AZ_MAX", "ES_ALT_MIN", "ES_ALT_MAX"):
        refs = {p[0] for p in data["nets"][es]}
        assert any(r.startswith("R") for r in refs) and any(r.startswith("C") for r in refs), es
